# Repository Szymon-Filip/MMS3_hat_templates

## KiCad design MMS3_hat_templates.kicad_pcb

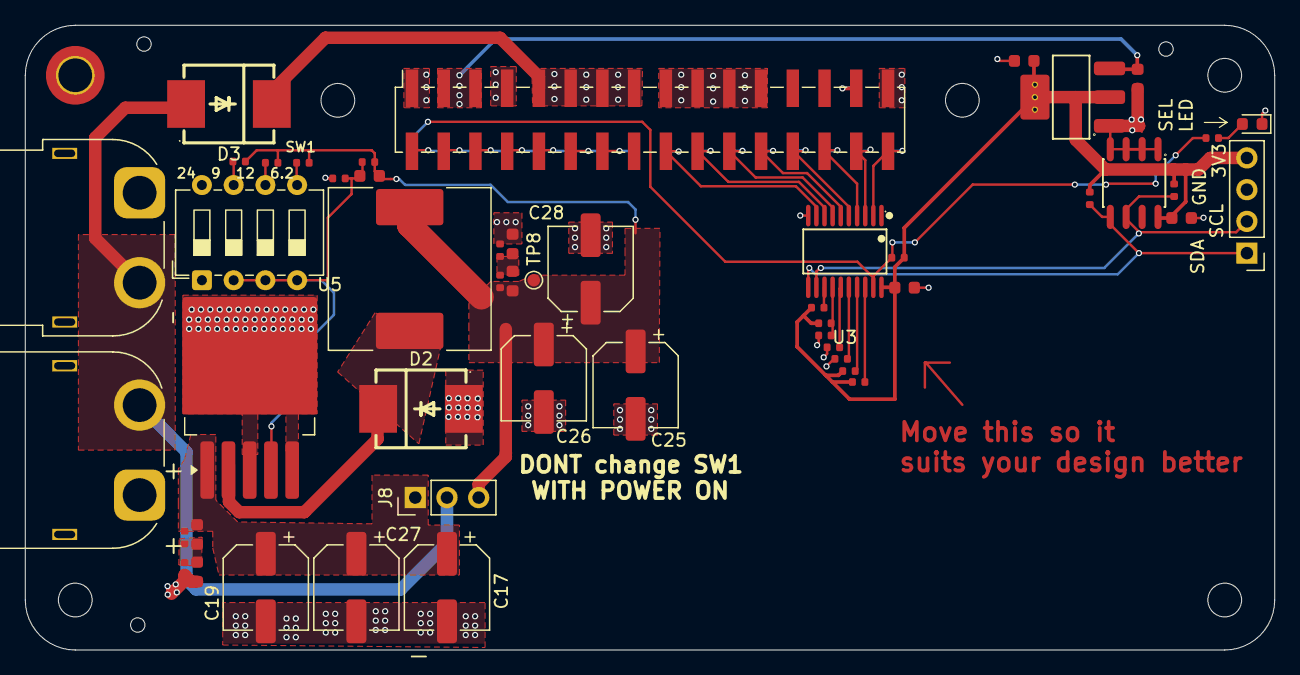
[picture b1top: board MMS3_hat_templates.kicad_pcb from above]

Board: 4 copper layers, 100.0 x 50.0 mm, 60 parts (1 on the bottom side), 40 nets.

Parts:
C1, C2, C20, C21, C23, C24: 100nF; C_0603
C16, C18: 10uF; C_0603
C17, C19, C25, C26, C27, C28: 47u; CP_Elec_6.3x7.7
C22: 3.3nF; C_0603
D1: LED; LED_0603_1608Metric
D2, D3: SS510C; SMC_L7.1-W6.2-LS8.1-RD
H1: M2.5 Mount; MountingHole_2.7mm_M2.5_DIN965_Pad_TopOnly
H2, H3, H4, H5, H6: M2.5 mount; MountingHole_2.7mm_M2.5
H7, H8, H9: Hole_Tooling_JLCPCB
J1: Chainbus in; PinHeader_2x16_P2.54mm_Vertical_SMD
J2: Chainbus Out; PinSocket_2x16_P2.54mm_Vertical_SMD
J3: Conn_01x04_Pin; PinHeader_1x04_P2.54mm_Vertical
J4: AMASS XT60 Male; AMASS_XT60PW-M_1x02_P7.20mm_Horizontal
J5: AMASS XT60 Female; AMASS_XT60PW-F_1x02_P7.20mm_Horizontal
J8: Conn_01x03_Pin; PinHeader_1x03_P2.54mm_Vertical
L1: 100uH 4A; L_Sunlord_SWRB1207S
R1: 330Ω; R_0402
R2, R3, R4, R5, R6, R7, R8, R9, R19, R20: 10kΩ; R_0402
R10, R11, R17, R18: 33kΩ; R_0402
R12: 1kΩ; R_0402
R13: 18.7k; R_0402
R14: 16.5k; R_0402
R15: 9.53k; R_0402
R16: 5.11k; R_0402
SW1: SW_DIP_x04; SW_DIP_SPSTx04_Slide_6.7x11.72mm_W7.62mm_P2.54mm_LowProfile
TP8: TestPoint; TestPoint_Pad_D1.0mm
U2: M24C64; SOIC-8_L5.0-W4.0-P1.27-LS6.0-BL
U3: SN74CB3Q3245PWR; TSSOP-20_L6.5-W4.4-P0.65-LS6.4-BL
U4: AMS1117; SOT-223-3_L6.5-W3.4-P2.30-LS7.0-BR
U5: LM2596HVS-ADJRG; TO-263-5_TabPin3

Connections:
+3V3: C1.1, C2.1, C18.1, J3.4, R2.1, R3.1, R4.2, R5.1, R6.1, R7.1, R8.1, U2.8 (VCC), U3.20 (VCC), U4.2 (VOUT), U4.4 (VOUT)
+5V: C16.1, J1.3, J1.5, J2.3, J2.5, U4.3 (VIN)
+12V stby: J1.29, J2.29
/Bus_switch/Chainbus.CS: R7.2, U3.13 (B6)
/Bus_switch/Chainbus.MISO: R19.1, U3.16 (B3)
/Bus_switch/Chainbus.MOSI: R20.1, U3.15 (B4)
/Bus_switch/Chainbus.RX: R5.2, U3.18 (B1)
/Bus_switch/Chainbus.SCK: R8.2, R9.1, U3.14 (B5)
/Bus_switch/Chainbus.SCL: J3.2, R2.2, U2.6 (SCL), U3.12 (B7)
/Bus_switch/Chainbus.SDA: J3.1, R3.2, U2.5 (SDA), U3.11 (B8)
/Bus_switch/Chainbus.TX: R6.2, U3.17 (B2)
/Bus_switch/Chainbus_In.CS: J1.22, J2.22, U3.7 (A6)
/Bus_switch/Chainbus_In.MISO: J1.28, J2.28, U3.4 (A3)
/Bus_switch/Chainbus_In.MOSI: J1.26, J2.26, U3.5 (A4)
/Bus_switch/Chainbus_In.RX: J1.32, J2.32, U3.2 (A1)
/Bus_switch/Chainbus_In.SCK: J1.24, J2.24, U3.6 (A5)
/Bus_switch/Chainbus_In.SCL: J1.20, J2.20, U3.8 (A7)
/Bus_switch/Chainbus_In.SDA: J1.18, J2.18, U3.9 (A8)
/Bus_switch/Chainbus_In.TX: J1.30, J2.30, U3.3 (A2)
/Bus_switch/SEL1: J1.2, R1.1, R4.1, U3.19 (~OE)
/Interboard_connector/SEL2: J1.4, J2.2
/Interboard_connector/SEL3: J1.6, J2.4
/Interboard_connector/SEL4: J1.8, J2.6
/Interboard_connector/SEL5: J1.10, J2.8
/Interboard_connector/SEL6: J1.12, J2.10
/Interboard_connector/SEL7: J1.14, J2.12
/Interboard_connector/SEL8: J1.16, J2.14
BRD_VIN: D3.1 (K), J1.9, J1.11, J1.13, J1.15, J2.9, J2.11, J2.13, J2.15
GND: C1.2, C2.2, C16.2, C17.2, C18.2, C19.2, C21.2, C24.2, C25.2, C26.2, C27.2, C28.2, D1.1 (K), D2.2 (A), H1.1, J1.1, J1.7, J1.17, J1.19, J1.21, J1.23, J1.31, J2.1, J2.7, J2.17, J2.19, J2.21, J2.23, J2.31, J3.3, J4.1, J5.1, R9.2, R11.2, R12.1, R18.2, R19.2, R20.2, U2.1 (A0), U2.2 (A1), U2.3 (A2), U2.4 (VSS), U3.10 (GND), U4.1 (GND), U5.3 (GND), U5.5 (~ON/OFF)
unnamed: C20.2, C21.1, R10.2, R11.1
unnamed: C23.2, C24.1, R17.2, R18.1
unnamed: D1.2 (A), R1.2
unnamed: D2.1 (K), L1.1, U5.2 (OUT)
unnamed: C17.1, C19.1, C20.1, C27.1, J8.1, R10.1, U5.1 (VIN)
unnamed: R14.1, SW1.7
unnamed: R15.1, SW1.6
unnamed: R16.1, SW1.5
unnamed: C22.1, R12.2, R13.1, SW1.2, SW1.3, SW1.4, U5.4 (FB)
U_reg: C22.2, C23.1, C25.1, C26.1, C28.1, J8.3, L1.2, R13.2, R14.2, R15.2, R16.2, R17.1, TP8.1
Vin: D3.2 (A), J4.2, J5.2, J8.2

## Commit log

2026-04-08 updated qr code to new repo
2026-04-08 removed jlcjlcjlc from silkscreen
2026-04-08 added rounded corners
